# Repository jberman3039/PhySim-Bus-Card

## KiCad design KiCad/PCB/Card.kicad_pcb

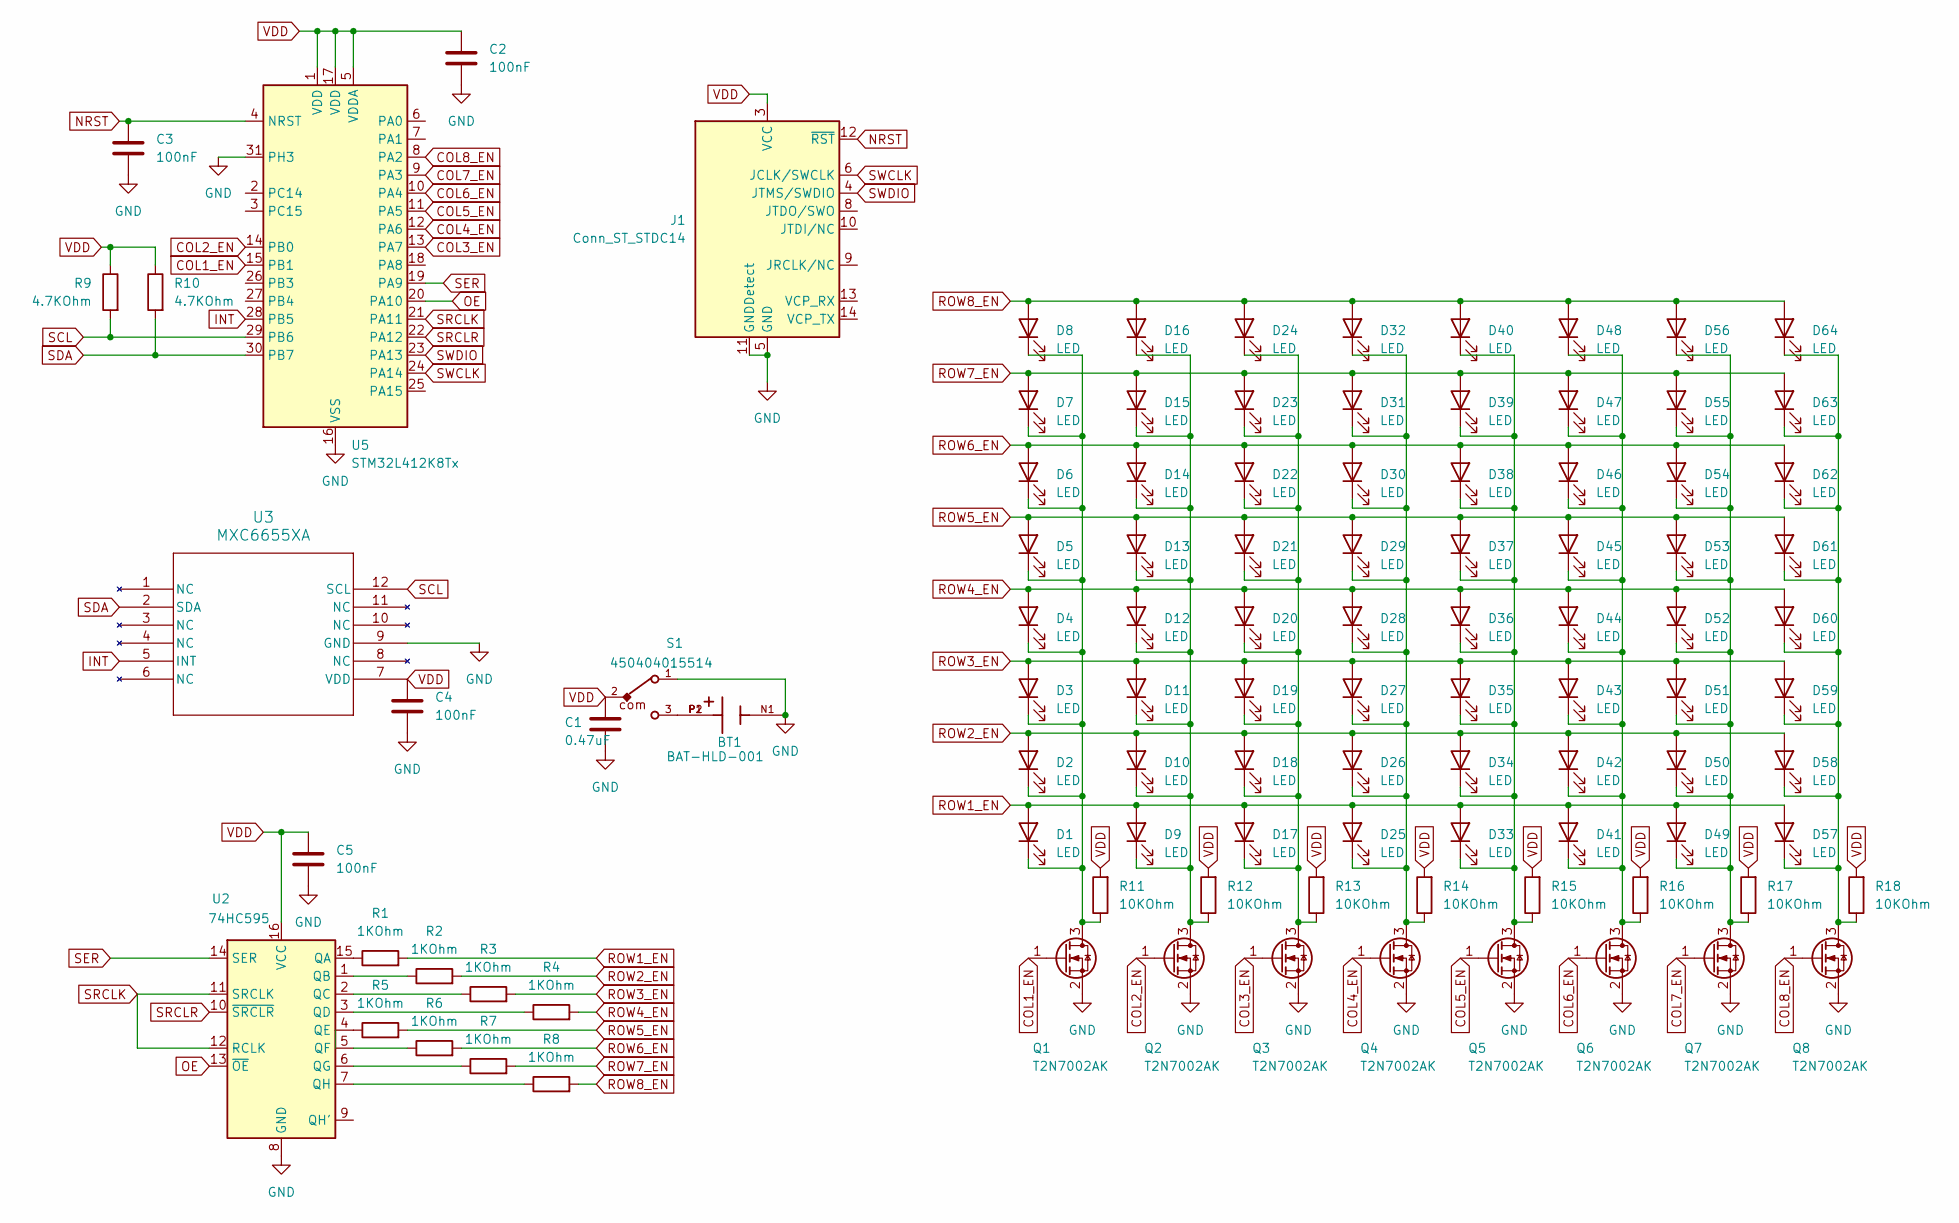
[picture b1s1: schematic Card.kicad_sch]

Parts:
BT1: BAT-HLD-001; BAT_BAT-HLD-001; PARTREV C
C1: 0.47uF; C_0805_2012Metric_Pad1.18x1.45mm_HandSolder
C2, C3, C4, C5: 100nF; C_0805_2012Metric_Pad1.18x1.45mm_HandSolder
D1, D2, D3, D4, D5, D6, D7, D8, D9, D10, D11, D12, D13, D14, D15, D16, D17, D18, D19, D20, D21, D22, D23, D24, D25, D26, D27, D28, D29, D30, D31, D32, D33, D34, D35, D36, D37, D38, D39, D40, D41, D42, D43, D44, D45, D46, D47, D48, D49, D50, D51, D52, D53, D54, D55, D56, D57, D58, D59, D60, D61, D62, D63, D64: LED; LED_0805_2012Metric_Pad1.15x1.40mm_HandSolder
J1: Conn_ST_STDC14; PinHeader_2x07_P1.27mm_Vertical
Q1, Q2, Q3, Q4, Q5, Q6, Q7, Q8: T2N7002AK; SOT-23
R1, R2, R3, R4, R5, R6, R7, R8: 1KOhm; R_0805_2012Metric_Pad1.20x1.40mm_HandSolder
R9, R10: 4.7KOhm; R_0805_2012Metric_Pad1.20x1.40mm_HandSolder
R11, R12, R13, R14, R15, R16, R17, R18: 10KOhm; R_0805_2012Metric_Pad1.20x1.40mm_HandSolder
S1: 450404015514
U2: 74HC595; SOIC-16_3.9x9.9mm_P1.27mm
U3: MXC6655XA; MXC6655XA_MEM
U5: STM32L412K8Tx; LQFP-32_7x7mm_P0.8mm

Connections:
COL1_EN: Q1.1 (G), U5.15 (PB1)
COL2_EN: Q2.1 (G), U5.14 (PB0)
COL3_EN: Q3.1 (G), U5.13 (PA7)
COL4_EN: Q4.1 (G), U5.12 (PA6)
COL5_EN: Q5.1 (G), U5.11 (PA5)
COL6_EN: Q6.1 (G), U5.10 (PA4)
COL7_EN: Q7.1 (G), U5.9 (PA3)
COL8_EN: Q8.1 (G), U5.8 (PA2)
GND: BT1.N1, C1.2, C2.2, C3.2, C4.2, C5.2, J1.5 (GND), J1.7 (GND), J1.11 (GNDDetect), Q1.2 (S), Q2.2 (S), Q3.2 (S), Q4.2 (S), Q5.2 (S), Q6.2 (S), Q7.2 (S), Q8.2 (S), S1.1, U2.8 (GND), U3.9 (GND), U5.16 (VSS), U5.31 (PH3), U5.32 (VSS)
INT: U3.5 (INT), U5.28 (PB5)
NRST: C3.1, J1.12 (~RST), U5.4 (NRST)
unnamed: BT1.P1, BT1.P2, S1.3
unnamed: D1.1 (K), D2.1 (K), D3.1 (K), D4.1 (K), D5.1 (K), D6.1 (K), D7.1 (K), D8.1 (K), Q1.3 (D), R11.1
unnamed: D9.1 (K), D10.1 (K), D11.1 (K), D12.1 (K), D13.1 (K), D14.1 (K), D15.1 (K), D16.1 (K), Q2.3 (D), R12.1
unnamed: D17.1 (K), D18.1 (K), D19.1 (K), D20.1 (K), D21.1 (K), D22.1 (K), D23.1 (K), D24.1 (K), Q3.3 (D), R13.1
unnamed: D25.1 (K), D26.1 (K), D27.1 (K), D28.1 (K), D29.1 (K), D30.1 (K), D31.1 (K), D32.1 (K), Q4.3 (D), R14.1
unnamed: D33.1 (K), D34.1 (K), D35.1 (K), D36.1 (K), D37.1 (K), D38.1 (K), D39.1 (K), D40.1 (K), Q5.3 (D), R15.1
unnamed: D41.1 (K), D42.1 (K), D43.1 (K), D44.1 (K), D45.1 (K), D46.1 (K), D47.1 (K), D48.1 (K), Q6.3 (D), R16.1
unnamed: D49.1 (K), D50.1 (K), D51.1 (K), D52.1 (K), D53.1 (K), D54.1 (K), D55.1 (K), D56.1 (K), Q7.3 (D), R17.1
unnamed: D57.1 (K), D58.1 (K), D59.1 (K), D60.1 (K), D61.1 (K), D62.1 (K), D63.1 (K), D64.1 (K), Q8.3 (D), R18.1
unnamed: R1.1, U2.15 (QA)
unnamed: R2.1, U2.1 (QB)
unnamed: R3.1, U2.2 (QC)
unnamed: R4.1, U2.3 (QD)
unnamed: R5.1, U2.4 (QE)
unnamed: R6.1, U2.5 (QF)
unnamed: R7.1, U2.6 (QG)
unnamed: R8.1, U2.7 (QH)
OE: U2.13 (~OE), U5.20 (PA10)
ROW1_EN: D1.2 (A), D9.2 (A), D17.2 (A), D25.2 (A), D33.2 (A), D41.2 (A), D49.2 (A), D57.2 (A), R1.2
ROW2_EN: D2.2 (A), D10.2 (A), D18.2 (A), D26.2 (A), D34.2 (A), D42.2 (A), D50.2 (A), D58.2 (A), R2.2
ROW3_EN: D3.2 (A), D11.2 (A), D19.2 (A), D27.2 (A), D35.2 (A), D43.2 (A), D51.2 (A), D59.2 (A), R3.2
ROW4_EN: D4.2 (A), D12.2 (A), D20.2 (A), D28.2 (A), D36.2 (A), D44.2 (A), D52.2 (A), D60.2 (A), R4.2
ROW5_EN: D5.2 (A), D13.2 (A), D21.2 (A), D29.2 (A), D37.2 (A), D45.2 (A), D53.2 (A), D61.2 (A), R5.2
ROW6_EN: D6.2 (A), D14.2 (A), D22.2 (A), D30.2 (A), D38.2 (A), D46.2 (A), D54.2 (A), D62.2 (A), R6.2
ROW7_EN: D7.2 (A), D15.2 (A), D23.2 (A), D31.2 (A), D39.2 (A), D47.2 (A), D55.2 (A), D63.2 (A), R7.2
ROW8_EN: D8.2 (A), D16.2 (A), D24.2 (A), D32.2 (A), D40.2 (A), D48.2 (A), D56.2 (A), D64.2 (A), R8.2
SCL: R9.2, U3.12 (SCL), U5.29 (PB6)
SDA: R10.2, U3.2 (SDA), U5.30 (PB7)
SER: U2.14 (SER), U5.19 (PA9)
SRCLK: U2.11 (SRCLK), U2.12 (RCLK), U5.21 (PA11)
SRCLR: U2.10 (~SRCLR), U5.22 (PA12)
SWCLK: J1.6 (JCLK/SWCLK), U5.24 (PA14)
SWDIO: J1.4 (JTMS/SWDIO), U5.23 (PA13)
VDD: C1.1, C2.1, C4.1, C5.1, J1.3 (VCC), R9.1, R10.1, R11.2, R12.2, R13.2, R14.2, R15.2, R16.2, R17.2, R18.2, S1.2, U2.16 (VCC), U3.7 (VDD), U5.1 (VDD), U5.5 (VDDA), U5.17 (VDD)

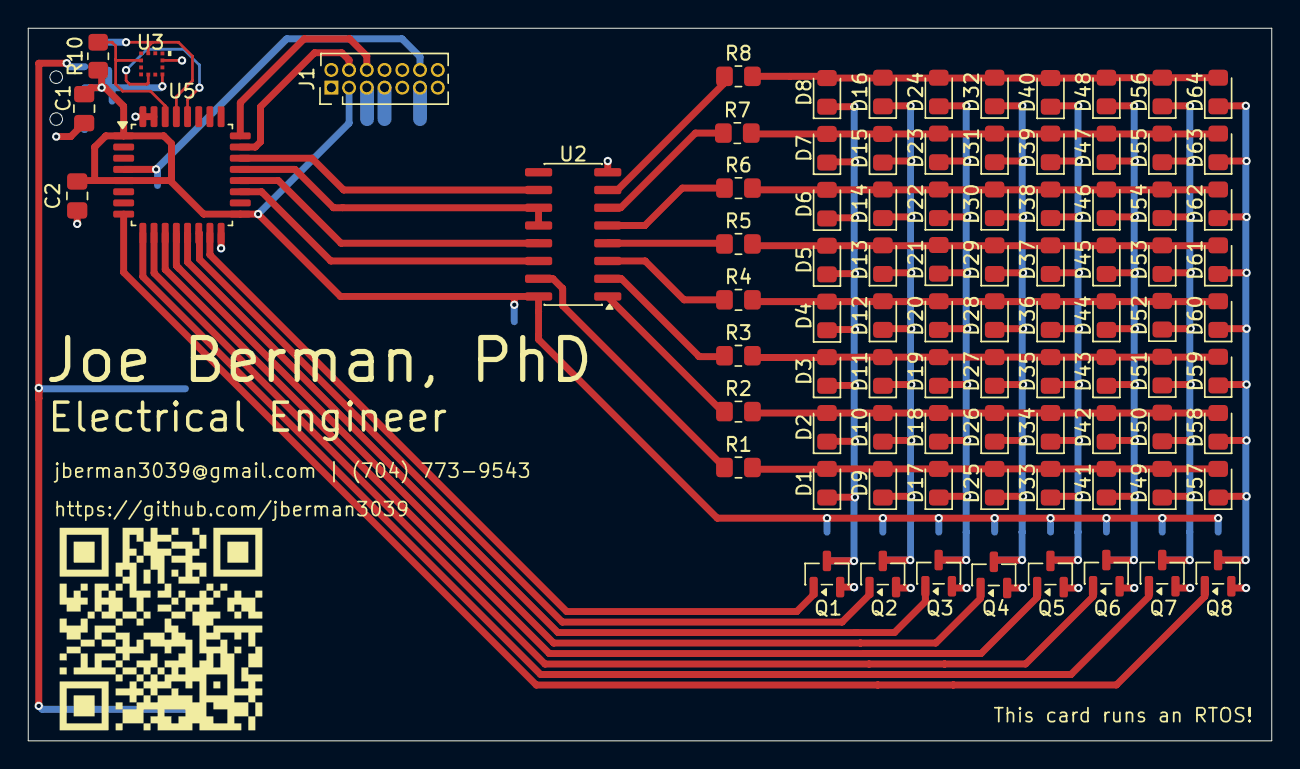
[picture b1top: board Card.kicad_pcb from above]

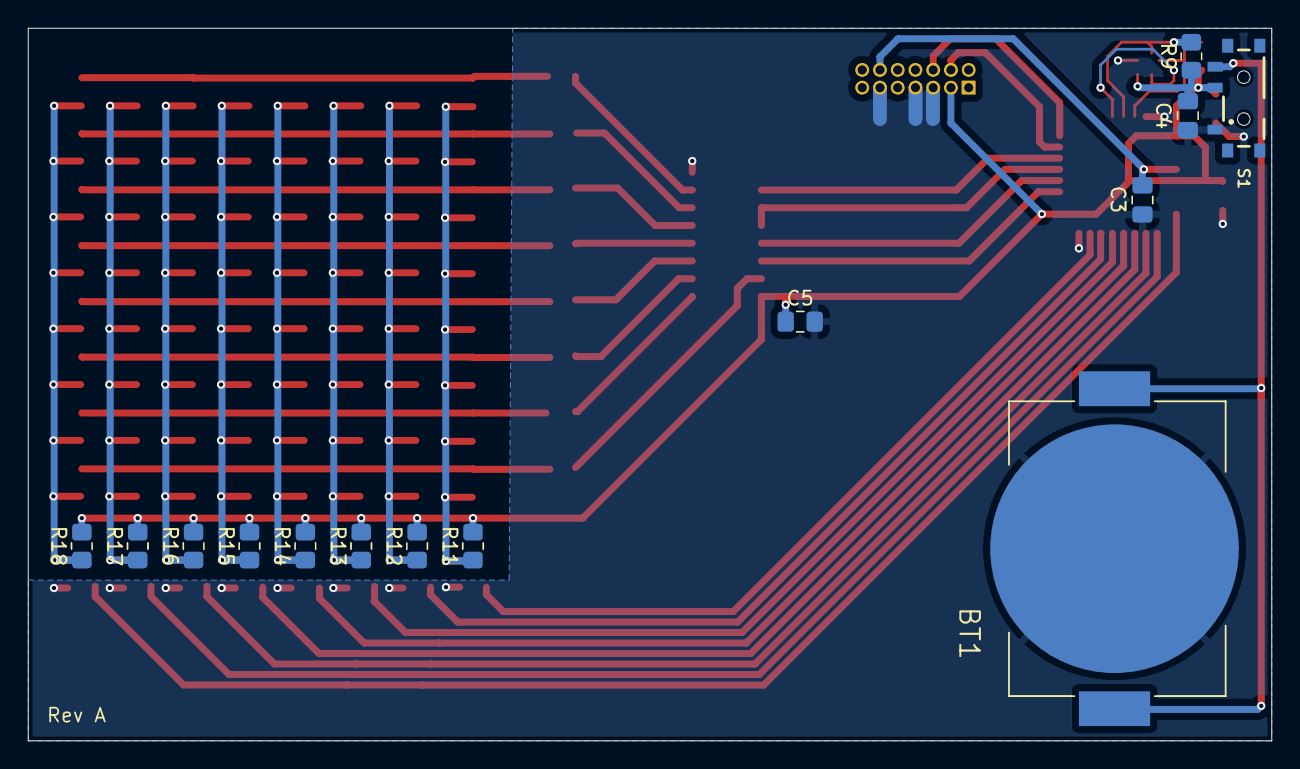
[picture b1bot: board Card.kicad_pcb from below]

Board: 2 copper layers, 89.0 x 51.0 mm, 102 parts (14 on the bottom side), 45 nets.

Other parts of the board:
QR*****: Github_QR

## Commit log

2025-11-29 adding PCB
2025-11-29 adding images folder
